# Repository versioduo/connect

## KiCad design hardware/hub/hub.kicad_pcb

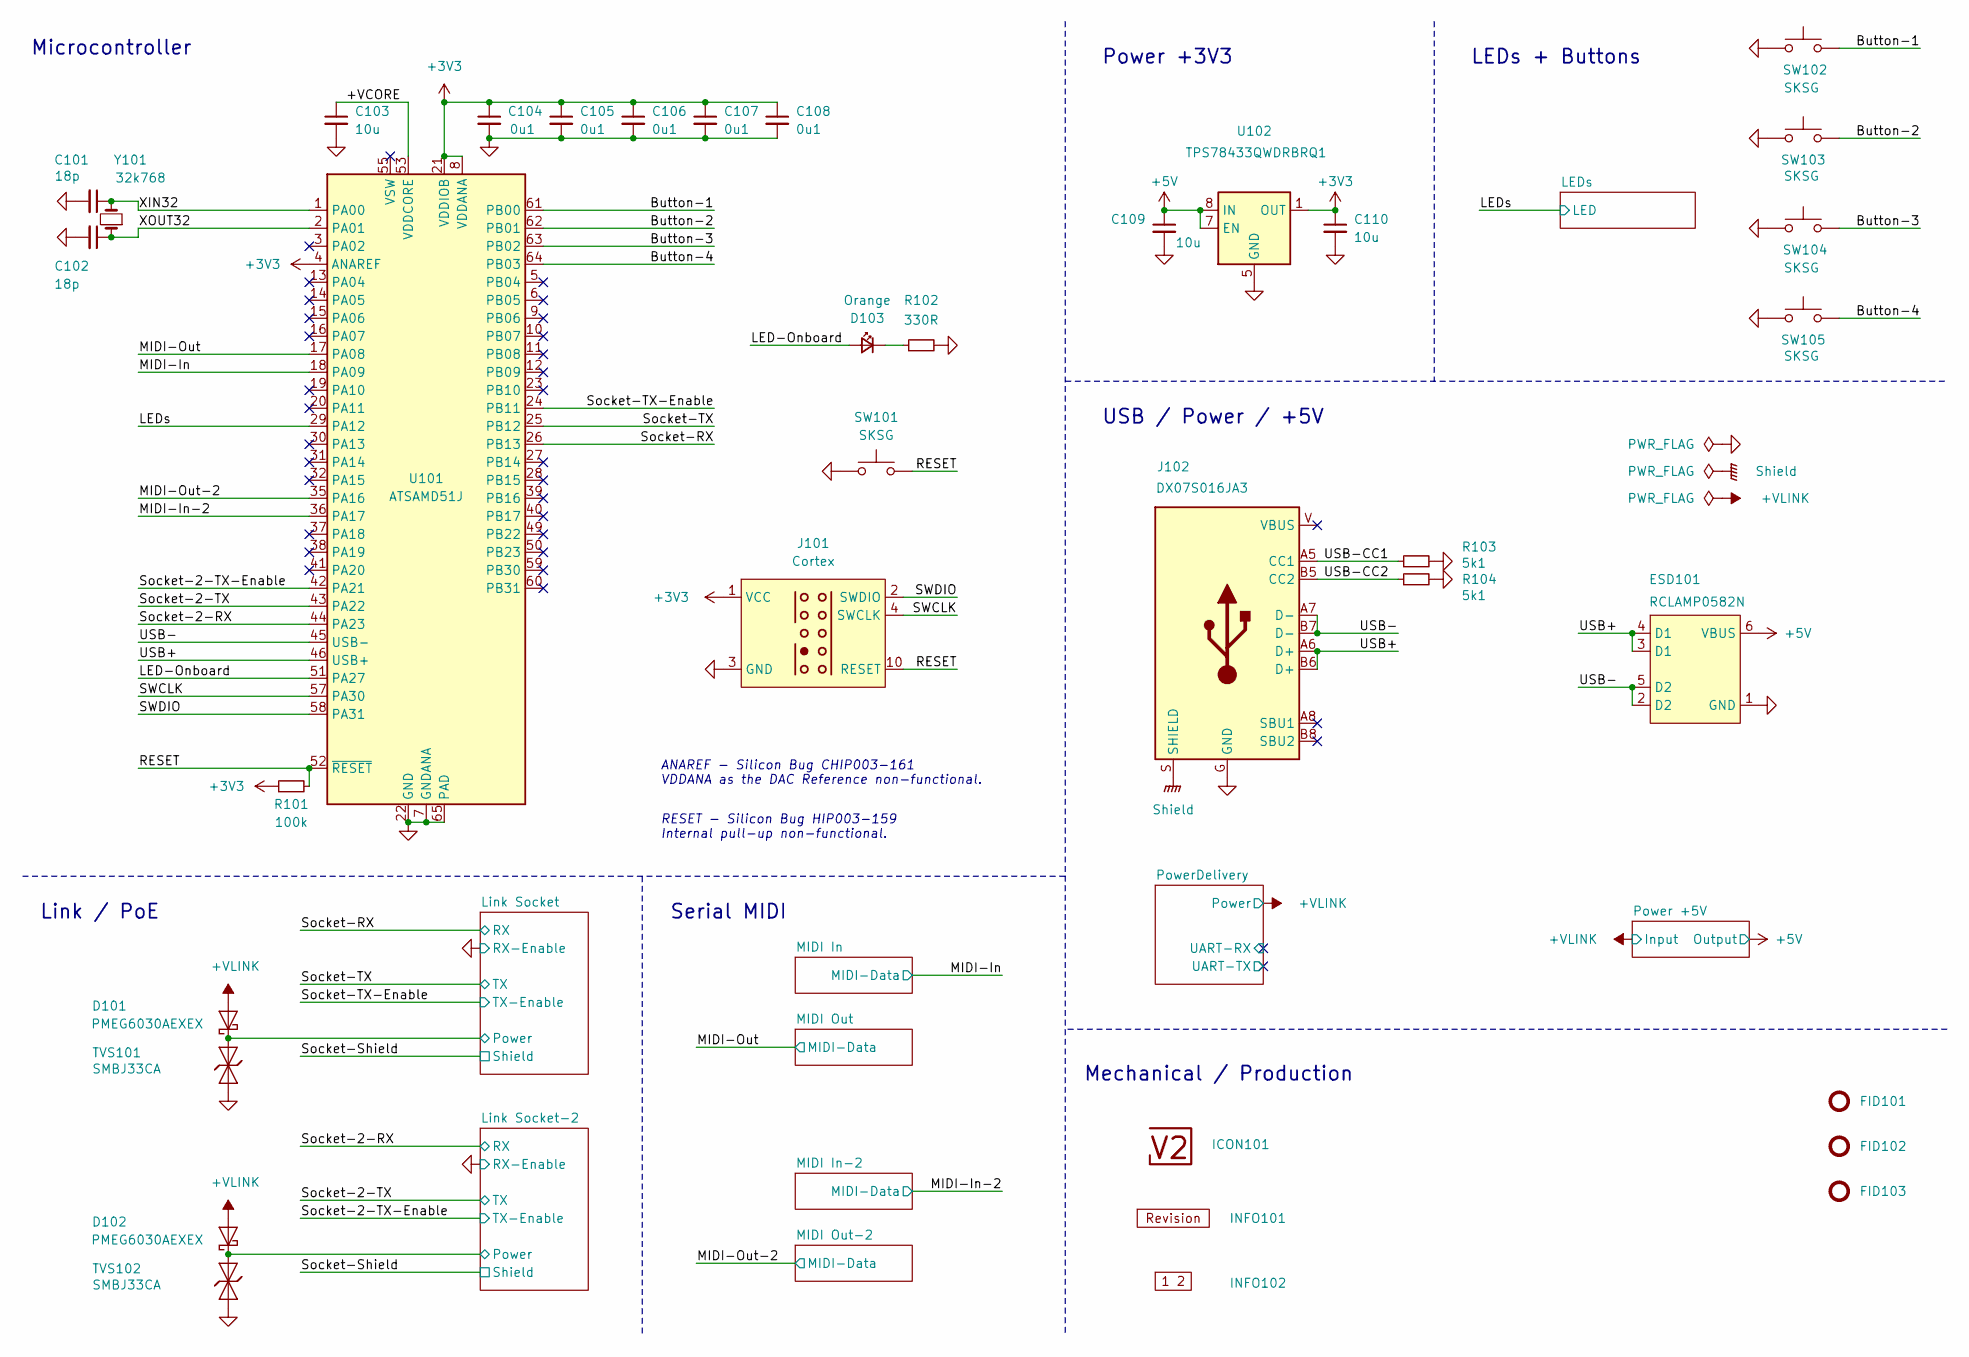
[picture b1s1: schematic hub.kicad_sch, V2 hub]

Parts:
C101, C102: 18p; C_1608; Rating 50V; Mouser 810-CGA3E2C0G1H180J
C103: 10u; C_1608; Rating 10V; Mouser 810-C1608X6S1A106M
C104, C105, C106, C107, C108: 0u1; C_1608; Rating 50V; Mouser 810-CGA3E2X7R1H104MA
C109, C110: 10u; C_2012; Rating 25V; Mouser 810-C2012X5R1E106K
D101, D102: PMEG6030AEXEX; D_SOD-123HP; Rating 60V; Mouser 771-PMEG6030AEXEX
D103: Orange; LED_1608; Rating 605nm; Mouser 755-SML-D12D1WT86
ESD101: RCLAMP0582N; SLP1210N6; Rating 20kV; Mouser 947-RCLAMP0582N.TCT
FID101, FID102, FID103: Fiducial_Paste; Fiducial_0.5mm_Mask1mm_Paste
ICON101: V2-logo; Logo_Small
INFO101: Revision
INFO102: Layer_Numbers-4
J101: Cortex
J102: DX07S016JA3; JAE_DX07S016JA3; Rating USB2.0; Mouser 656-DX07S016JA3R1500
R101: 100k; R_1608; Rating 100mW; Mouser 71-CRCW0603100KFKEAC
R102: 330R; R_1608; Rating 100mW; Mouser 71-CRCW0603330RFKEAC
R103, R104: 5k1; R_1608; Rating 100mW; Mouser 71-CRCW06035K10FKEAC
SW101, SW102, SW103, SW104, SW105: SKSG; Rating 1.6N; Mouser 688-SKSGACE010
TVS101, TVS102: SMBJ33CA; D_SMB; Rating 33V; Mouser 652-SMBJ33CA-Q
U101: ATSAMD51J; QFN-64-1EP_9x9mm_P0.5mm_EP4.8x4.8mm_ThermalVias; Rating Cortex-M4F; Mouser 556-ATSAMD51J19AMU
U102: TPS78433QWDRBRQ1; VSON-8-1_3x3mm_P0.65_EP1.65x2.4mm; Rating 300mA; Mouser 595-TPS78433QWDRBRQ1
Y101: 32k768; Crystal_SMD_3215-2Pin_3.2x1.5mm; Rating 10ppm; Mouser 815-ABS0716632.768KT

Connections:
+3V3: C104.1, C105.1, C106.1, C107.1, C108.1, C110.1, J101.1 (VCC), R101.1, U101.4 (ANAREF), U101.8 (VDDANA), U101.21 (VDDIOB), U101.34 (VDDIO), U101.48 (VDDIO), U101.56 (VDDIO), U102.1 (OUT); also elsewhere on the board
+5V: C109.1, ESD101.6 (VBUS), U102.7 (EN), U102.8 (IN); also elsewhere on the board
/+VCORE: C103.1, U101.53 (VDDCORE)
/+VLINK: D101.2 (A), D102.2 (A); also elsewhere on the board
/Button-1: SW102.2, U101.61 (PB00)
/Button-2: SW103.2, U101.62 (PB01)
/Button-3: SW104.2, U101.63 (PB02)
/Button-4: SW105.2, U101.64 (PB03)
/LED-Onboard: D103.2 (A), U101.51 (PA27)
/LEDs: U101.29 (PA12); also elsewhere on the board
/Link Socket-2/Power: D102.1 (K), TVS102.2 (A); also elsewhere on the board
/Link Socket/Power: D101.1 (K), TVS101.2 (A); also elsewhere on the board
/MIDI-In: U101.18 (PA09); also elsewhere on the board
/MIDI-In-2: U101.36 (PA17); also elsewhere on the board
/MIDI-Out: U101.17 (PA08); also elsewhere on the board
/MIDI-Out-2: U101.35 (PA16); also elsewhere on the board
/RESET: J101.10 (RESET), R101.2, SW101.2, U101.52 (~RESET)
/SWCLK: J101.4 (SWCLK), U101.57 (PA30)
/SWDIO: J101.2 (SWDIO), U101.58 (PA31)
/Shield: J102.S (SHIELD)
/Socket-2-RX: U101.44 (PA23); also elsewhere on the board
/Socket-2-TX: U101.43 (PA22); also elsewhere on the board
/Socket-2-TX-Enable: U101.42 (PA21); also elsewhere on the board
/Socket-RX: U101.26 (PB13); also elsewhere on the board
/Socket-TX: U101.25 (PB12); also elsewhere on the board
/Socket-TX-Enable: U101.24 (PB11); also elsewhere on the board
/USB+: ESD101.3 (D1), ESD101.4 (D1), J102.A6 (D+), J102.B6 (D+), U101.46 (USB+)
/USB-: ESD101.2 (D2), ESD101.5 (D2), J102.A7 (D-), J102.B7 (D-), U101.45 (USB-)
/USB-CC1: J102.A5 (CC1), R103.1
/USB-CC2: J102.B5 (CC2), R104.1
/XIN32: C101.1, U101.1 (PA00), Y101.2
/XOUT32: C102.1, U101.2 (PA01), Y101.1
GND: C101.2, C102.2, C103.2, C104.2, C105.2, C106.2, C107.2, C108.2, C109.2, C110.2, ESD101.1 (GND), J101.3 (GND), J101.5 (GND), J102.G (GND), R102.2, R103.2, R104.2, SW101.1, SW102.1, SW103.1, SW104.1, SW105.1, TVS101.1 (K), TVS102.1 (K), U101.7 (GNDANA), U101.22 (GND), U101.33 (GND), U101.47 (GND), U101.54 (GND), U101.65 (PAD), U102.5 (GND), U102.9 (GND); also elsewhere on the board
unnamed: D103.1 (K), R102.1

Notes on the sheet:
ANAREF - Silicon Bug CHIP003-161 VDDANA as the DAC Reference non-functional.
Link / PoE
RESET - Silicon Bug HIP003-159 Internal pull-up non-functional.
LEDs + Buttons
Serial MIDI
Power +3V3
Mechanical / Production
Microcontroller
USB / Power / +5V

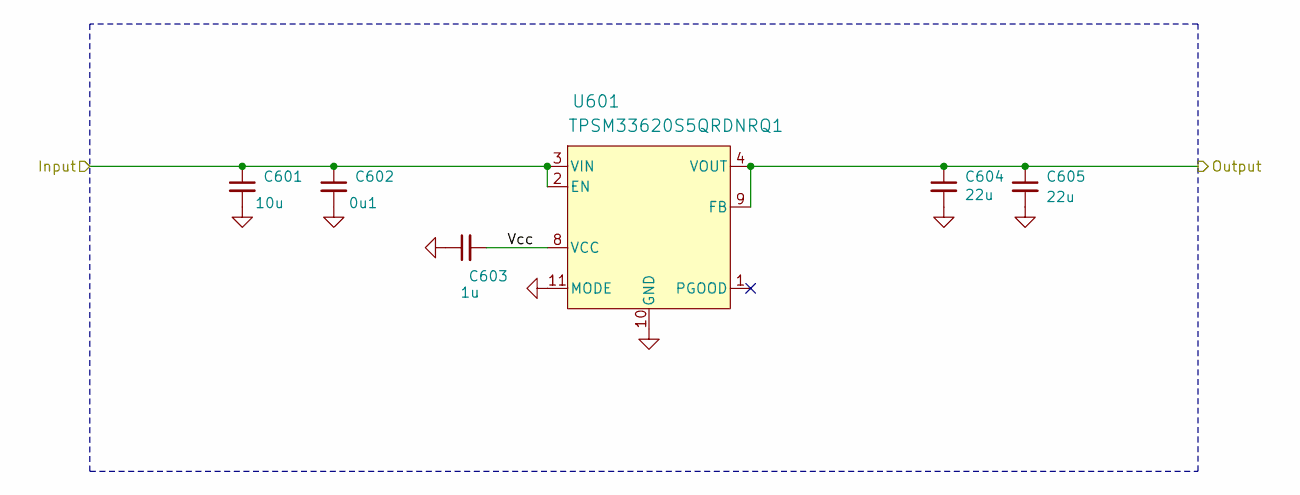
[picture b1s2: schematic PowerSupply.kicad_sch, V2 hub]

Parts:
C601: 10u; C_3225; Rating 50V; Mouser 810-CNC6P1X7R1H106K2
C602: 0u1; C_1608; Rating 50V; Mouser 810-CGA3E2X7R1H104MA
C603: 1u; C_1608; Rating 50V; Mouser 810-CGA3E3X7R1H105K0
C604, C605: 22u; C_3225; Rating 25V; Mouser 810-CGA6P3X7R1E226M5
U601: TPSM33620S5QRDNRQ1; QFN-11; Rating 2A; Mouser 595-SM33620S5QRDNRQ1

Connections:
+5V: C604.1, C605.1, U601.4 (VOUT), U601.9 (FB); also elsewhere on the board
/+VLINK: C601.1, C602.1, U601.2 (EN), U601.3 (VIN); also elsewhere on the board
/Power +5V/Vcc: C603.2, U601.8 (VCC)
GND: C601.2, C602.2, C603.1, C604.2, C605.2, U601.10 (GND), U601.11 (MODE); also elsewhere on the board

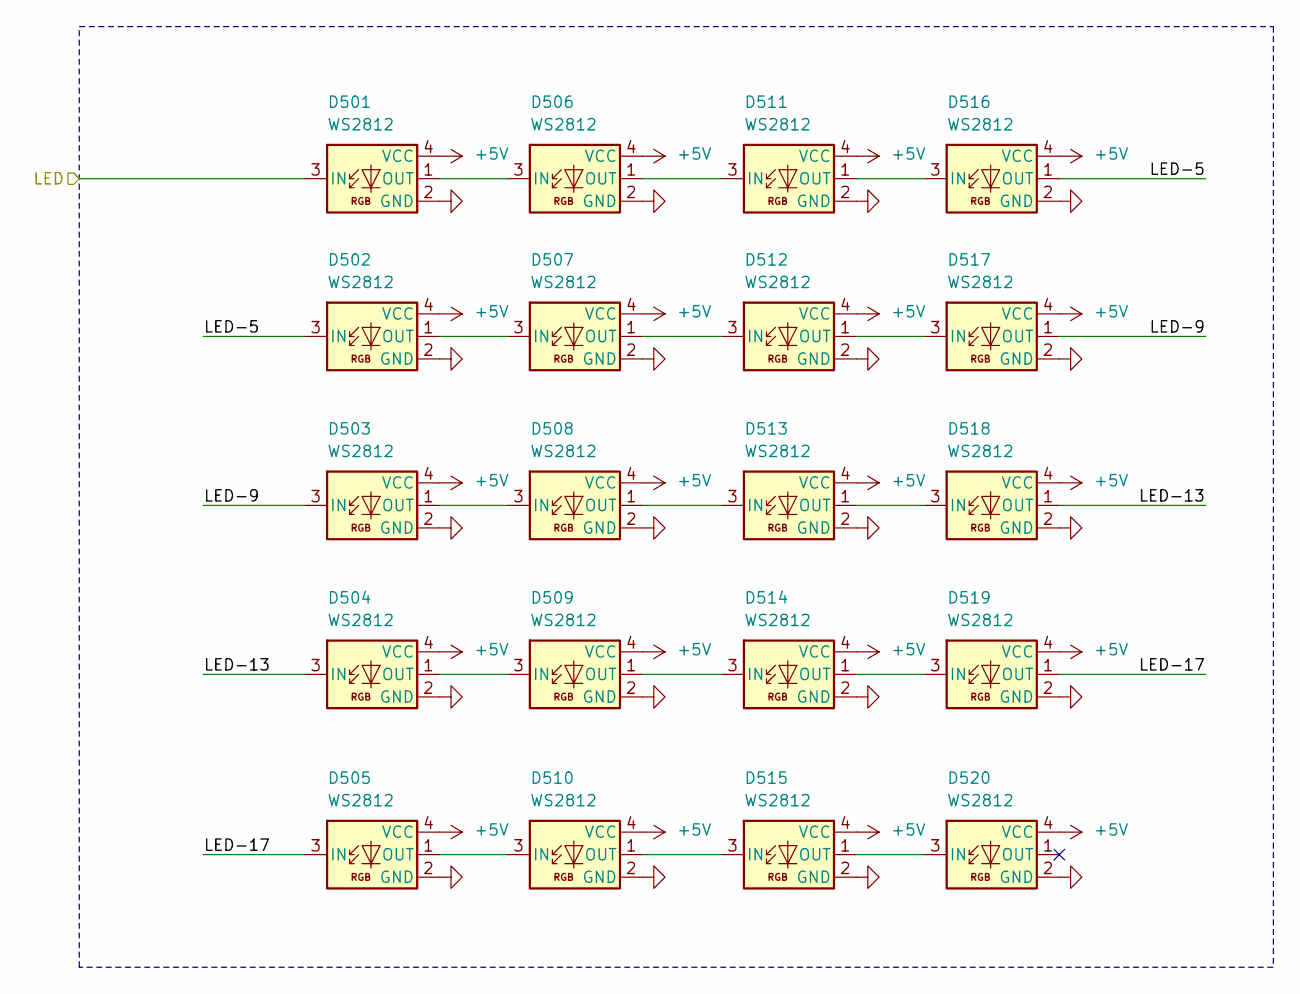
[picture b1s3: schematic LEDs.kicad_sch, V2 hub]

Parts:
D501, D502, D503, D504, D505, D506, D507, D508, D509, D510, D511, D512, D513, D514, D515, D516, D517, D518, D519, D520: WS2812; WS2812-2020; Rating 15mA; LCSC C965555

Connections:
+5V: D501.4 (VCC), D502.4 (VCC), D503.4 (VCC), D504.4 (VCC), D505.4 (VCC), D506.4 (VCC), D507.4 (VCC), D508.4 (VCC), D509.4 (VCC), D510.4 (VCC), D511.4 (VCC), D512.4 (VCC), D513.4 (VCC), D514.4 (VCC), D515.4 (VCC), D516.4 (VCC), D517.4 (VCC), D518.4 (VCC), D519.4 (VCC), D520.4 (VCC); also elsewhere on the board
/LEDs: D501.3 (IN); also elsewhere on the board
/LEDs/LED-5: D502.3 (IN), D516.1 (OUT)
/LEDs/LED-9: D503.3 (IN), D517.1 (OUT)
/LEDs/LED-13: D504.3 (IN), D518.1 (OUT)
/LEDs/LED-17: D505.3 (IN), D519.1 (OUT)
GND: D501.2 (GND), D502.2 (GND), D503.2 (GND), D504.2 (GND), D505.2 (GND), D506.2 (GND), D507.2 (GND), D508.2 (GND), D509.2 (GND), D510.2 (GND), D511.2 (GND), D512.2 (GND), D513.2 (GND), D514.2 (GND), D515.2 (GND), D516.2 (GND), D517.2 (GND), D518.2 (GND), D519.2 (GND), D520.2 (GND); also elsewhere on the board
unnamed: D501.1 (OUT), D506.3 (IN)
unnamed: D502.1 (OUT), D507.3 (IN)
unnamed: D503.1 (OUT), D508.3 (IN)
unnamed: D504.1 (OUT), D509.3 (IN)
unnamed: D505.1 (OUT), D510.3 (IN)
unnamed: D506.1 (OUT), D511.3 (IN)
unnamed: D507.1 (OUT), D512.3 (IN)
unnamed: D508.1 (OUT), D513.3 (IN)
unnamed: D509.1 (OUT), D514.3 (IN)
unnamed: D510.1 (OUT), D515.3 (IN)
unnamed: D511.1 (OUT), D516.3 (IN)
unnamed: D512.1 (OUT), D517.3 (IN)
unnamed: D513.1 (OUT), D518.3 (IN)
unnamed: D514.1 (OUT), D519.3 (IN)
unnamed: D515.1 (OUT), D520.3 (IN)

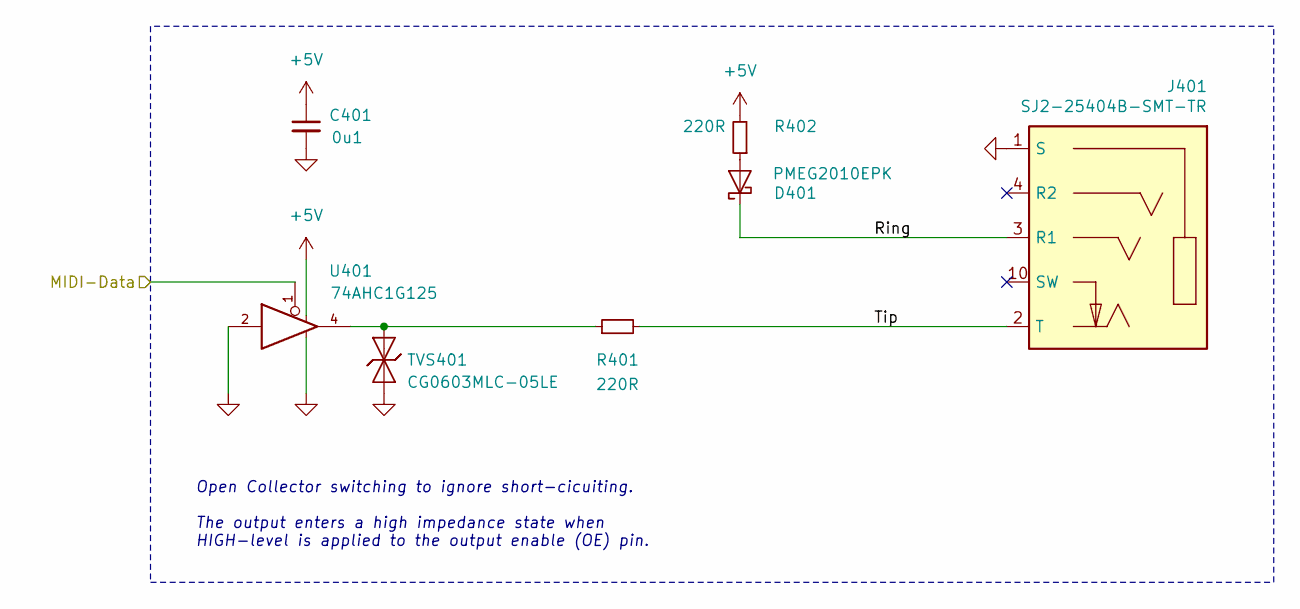
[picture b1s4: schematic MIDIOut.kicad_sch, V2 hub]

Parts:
C401: 0u1; C_1608; Rating 50V; Mouser 810-CGA3E2X7R1H104MA
D401: PMEG2010EPK; D_SOD-1608; Rating 20V; Mouser 771-PMEG2010EPK
J401: SJ2-25404B-SMT-TR; CUI_SJ2-25404B-SMT-TR; Rating 2.5mm; Mouser 490-SJ2-25404BSMT-TR
R401, R402: 220R; R_1608; Rating 330mW; Mouser 71-CRCW0603220RFKEAH
TVS401: CG0603MLC-05LE; D_1608; Rating 5V; Mouser 652-CG0603MLC-05LE
U401: 74AHC1G125; SOT-23-5; Rating 8mA; Mouser 595-SN74AHC1G125DBVR

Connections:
+5V: C401.1, R402.2, U401.5; also elsewhere on the board
/MIDI Out/Ring: D401.1 (K), J401.3 (R1)
/MIDI Out/Tip: J401.2 (T), R401.2
/MIDI-Out: U401.1; also elsewhere on the board
GND: C401.2, J401.1 (S), TVS401.1 (K), U401.2, U401.3; also elsewhere on the board
unnamed: D401.2 (A), R402.1
unnamed: R401.1, TVS401.2 (A), U401.4

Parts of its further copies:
C901: 0u1; C_1608; Rating 50V; Mouser 810-CGA3E2X7R1H104MA
D901: PMEG2010EPK; D_SOD-1608; Rating 20V; Mouser 771-PMEG2010EPK
J901: SJ2-25404B-SMT-TR; CUI_SJ2-25404B-SMT-TR; Rating 2.5mm; Mouser 490-SJ2-25404BSMT-TR
R901, R902: 220R; R_1608; Rating 330mW; Mouser 71-CRCW0603220RFKEAH
TVS901: CG0603MLC-05LE; D_1608; Rating 5V; Mouser 652-CG0603MLC-05LE
U901: 74AHC1G125; SOT-23-5; Rating 8mA; Mouser 595-SN74AHC1G125DBVR

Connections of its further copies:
+5V: C901.1, R902.2, U901.5; also elsewhere on the board
/MIDI Out-2/Ring: D901.1 (K), J901.3 (R1)
/MIDI Out-2/Tip: J901.2 (T), R901.2
/MIDI-Out-2: U901.1; also elsewhere on the board
GND: C901.2, J901.1 (S), TVS901.1 (K), U901.2, U901.3; also elsewhere on the board
unnamed: D901.2 (A), R902.1
unnamed: R901.1, TVS901.2 (A), U901.4

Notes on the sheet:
﻿Open Collector switching to ignore short-cicuiting. The output enters a high impedance state when HIGH-level is applied to the output enable (OE) pin.

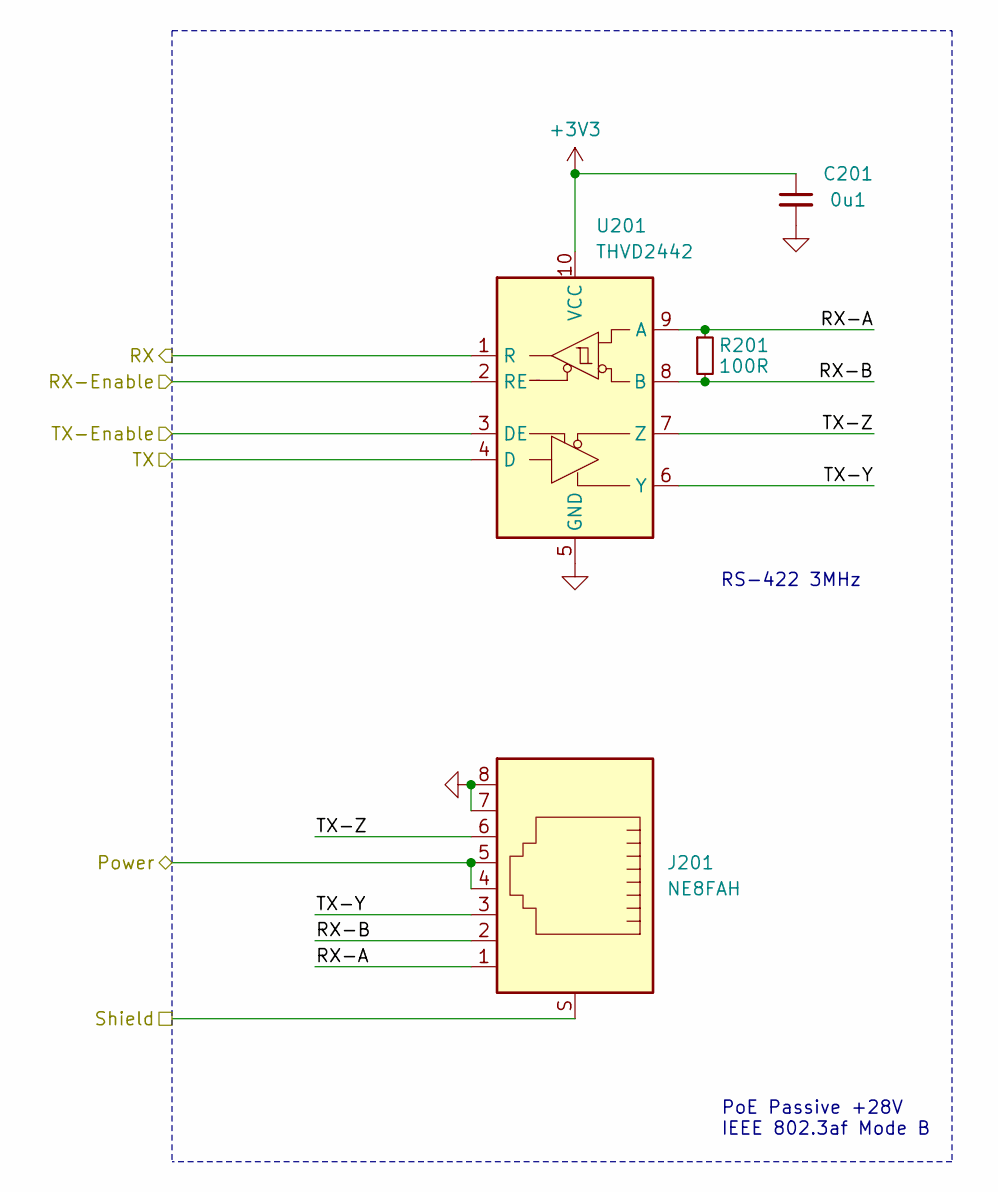
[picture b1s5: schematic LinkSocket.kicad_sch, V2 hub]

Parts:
C201: 0u1; C_1608; Rating 50V; Mouser 810-CGA3E2X7R1H104MA
J201: NE8FAH; Rating CAT5e; Mouser 568-NE8FAH
R201: 100R; R_1608; Rating 330mW; Mouser 71-CRCW0603100RFKEAH
U201: THVD2442; VSON-10-4-1EP_3x3mm_P0.5mm_EP1.65x2.4mm_ThermalVias; Rating 20Mbps; Mouser 595-THVD2442DRCR

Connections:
+3V3: C201.1, U201.10 (VCC); also elsewhere on the board
/Link Socket/Power: J201.4, J201.5; also elsewhere on the board
/Link Socket/RX-A: J201.1, R201.1, U201.9 (A)
/Link Socket/RX-B: J201.2, R201.2, U201.8 (B)
/Link Socket/TX-Y: J201.3, U201.6 (Y)
/Link Socket/TX-Z: J201.6, U201.7 (Z)
/Socket-RX: U201.1 (R); also elsewhere on the board
/Socket-Shield: J201.S; also elsewhere on the board
/Socket-TX: U201.4 (D); also elsewhere on the board
/Socket-TX-Enable: U201.3 (DE); also elsewhere on the board
GND: C201.2, J201.7, J201.8, U201.2 (RE), U201.5 (GND), U201.11 (GND); also elsewhere on the board

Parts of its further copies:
C701: 0u1; C_1608; Rating 50V; Mouser 810-CGA3E2X7R1H104MA
J701: NE8FAH; Rating CAT5e; Mouser 568-NE8FAH
R701: 100R; R_1608; Rating 330mW; Mouser 71-CRCW0603100RFKEAH
U701: THVD2442; VSON-10-4-1EP_3x3mm_P0.5mm_EP1.65x2.4mm_ThermalVias; Rating 20Mbps; Mouser 595-THVD2442DRCR

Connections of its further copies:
+3V3: C701.1, U701.10 (VCC); also elsewhere on the board
/Link Socket-2/Power: J701.4, J701.5; also elsewhere on the board
/Link Socket-2/RX-A: J701.1, R701.1, U701.9 (A)
/Link Socket-2/RX-B: J701.2, R701.2, U701.8 (B)
/Link Socket-2/TX-Y: J701.3, U701.6 (Y)
/Link Socket-2/TX-Z: J701.6, U701.7 (Z)
/Socket-2-RX: U701.1 (R); also elsewhere on the board
/Socket-2-TX: U701.4 (D); also elsewhere on the board
/Socket-2-TX-Enable: U701.3 (DE); also elsewhere on the board
/Socket-Shield: J701.S; also elsewhere on the board
GND: C701.2, J701.7, J701.8, U701.2 (RE), U701.5 (GND), U701.11 (GND); also elsewhere on the board

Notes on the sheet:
PoE Passive +28V IEEE 802.3af Mode B
RS-422 3MHz

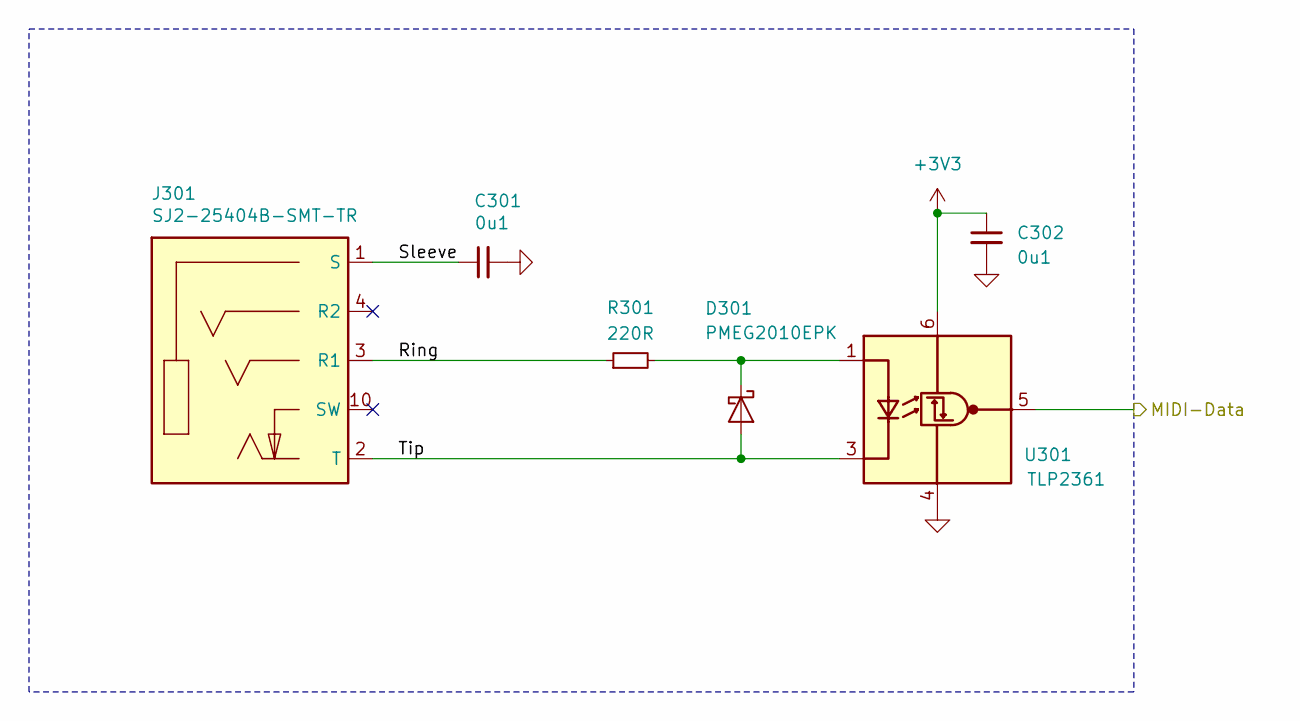
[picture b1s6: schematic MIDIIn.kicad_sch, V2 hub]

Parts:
C301, C302: 0u1; C_1608; Rating 50V; Mouser 810-CGA3E2X7R1H104MA
D301: PMEG2010EPK; D_SOD-1608; Rating 20V; Mouser 771-PMEG2010EPK
J301: SJ2-25404B-SMT-TR; CUI_SJ2-25404B-SMT-TR; Rating 2.5mm; Mouser 490-SJ2-25404BSMT-TR
R301: 220R; R_1608; Rating 330mW; Mouser 71-CRCW0603220RFKEAH
U301: TLP2361; SO-5-6_4.55x3.7mm_P1.27mm; Rating 15Mbps; Mouser 757-TLP2361TPRE

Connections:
+3V3: C302.1, U301.6 (VDD); also elsewhere on the board
/MIDI In/Ring: J301.3 (R1), R301.1
/MIDI In/Sleeve: C301.1, J301.1 (S)
/MIDI In/Tip: D301.2 (A), J301.2 (T), U301.3 (K)
/MIDI-In: U301.5 (VO); also elsewhere on the board
GND: C301.2, C302.2, U301.4 (GND); also elsewhere on the board
unnamed: D301.1 (K), R301.2, U301.1 (A)

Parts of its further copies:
C801, C802: 0u1; C_1608; Rating 50V; Mouser 810-CGA3E2X7R1H104MA
D801: PMEG2010EPK; D_SOD-1608; Rating 20V; Mouser 771-PMEG2010EPK
J801: SJ2-25404B-SMT-TR; CUI_SJ2-25404B-SMT-TR; Rating 2.5mm; Mouser 490-SJ2-25404BSMT-TR
R801: 220R; R_1608; Rating 330mW; Mouser 71-CRCW0603220RFKEAH
U801: TLP2361; SO-5-6_4.55x3.7mm_P1.27mm; Rating 15Mbps; Mouser 757-TLP2361TPRE

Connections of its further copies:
+3V3: C802.1, U801.6 (VDD); also elsewhere on the board
/MIDI In-2/Ring: J801.3 (R1), R801.1
/MIDI In-2/Sleeve: C801.1, J801.1 (S)
/MIDI In-2/Tip: D801.2 (A), J801.2 (T), U801.3 (K)
/MIDI-In-2: U801.5 (VO); also elsewhere on the board
GND: C801.2, C802.2, U801.4 (GND); also elsewhere on the board
unnamed: D801.1 (K), R801.2, U801.1 (A)

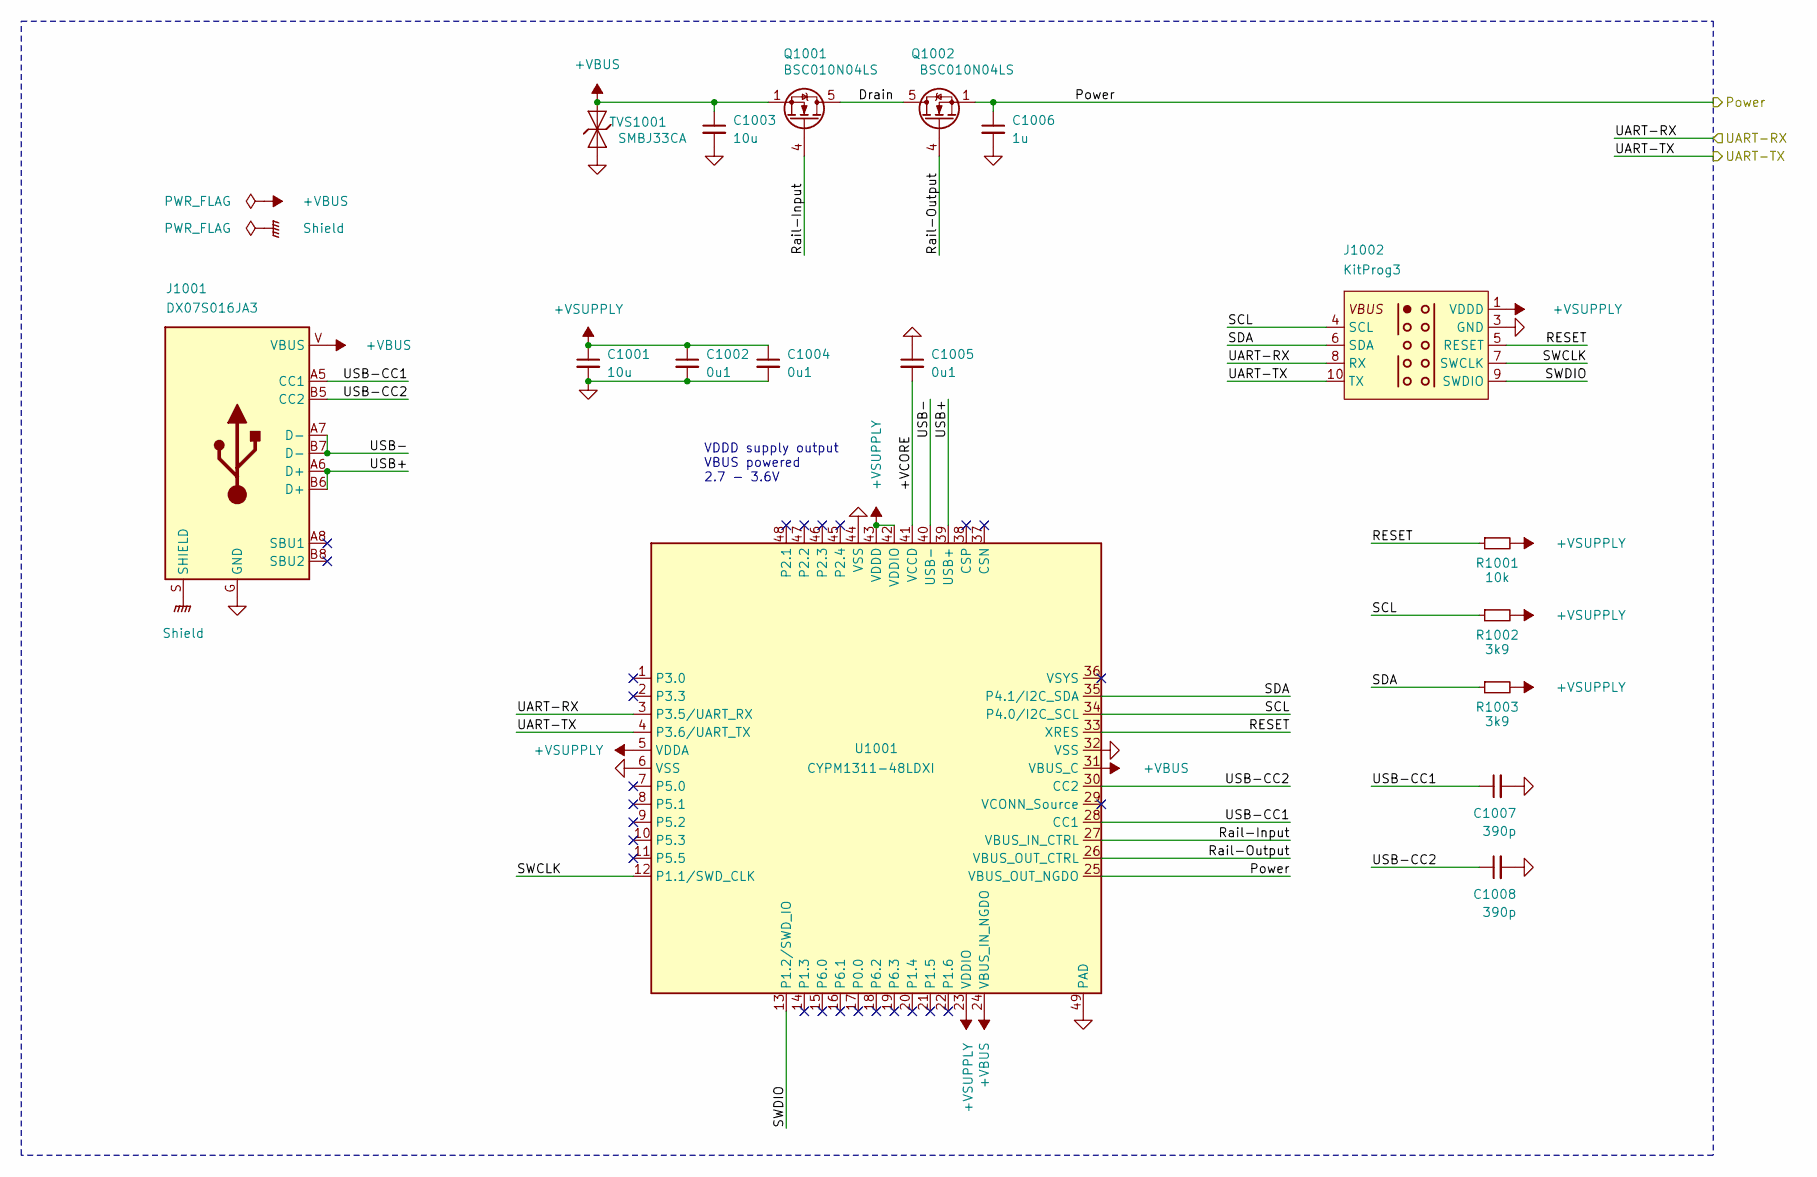
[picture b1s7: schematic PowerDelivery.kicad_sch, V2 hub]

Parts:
C1001: 10u; C_1608; Rating 10V; Mouser 810-C1608X6S1A106M
C1002, C1004, C1005: 0u1; C_1608; Rating 50V; Mouser 810-CGA3E2X7R1H104MA
C1003: 10u; C_2012; Rating 25V; Mouser 810-C2012X5R1E106K
C1006: 1u; C_1608; Rating 50V; Mouser 810-CGA3E3X7R1H105K0
C1007, C1008: 390p; C_1608; Rating 50V; Mouser 810-CGA3E2C0G1H391J
J1001: DX07S016JA3; JAE_DX07S016JA3; Rating USB2.0; Mouser 656-DX07S016JA3R1500
J1002: KitProg3
Q1001, Q1002: BSC010N04LS; TDSON-8-FL; Rating 40V; Mouser 726-BSC010N04LS
R1001: 10k; R_1608; Rating 100mW; Mouser 71-CRCW060310K0FKEAC
R1002, R1003: 3k9; R_1608; Rating 100mW; Mouser 71-CRCW06033K90FKEAC
TVS1001: SMBJ33CA; D_SMB; Rating 33V; Mouser 652-SMBJ33CA-Q
U1001: CYPM1311-48LDXI; QFN-48-1EP_6x6mm_P0.4mm_EP4.6x4.6mm; Rating 28V; Mouser 727-CYPM1311-48LDXI

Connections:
/+VLINK: C1006.1, Q1002.1 (S), U1001.25 (VBUS_OUT_NGDO); also elsewhere on the board
/PowerDelivery/+VBUS: C1003.1, J1001.V (VBUS), Q1001.1 (S), TVS1001.2 (A), U1001.24 (VBUS_IN_NGDO), U1001.31 (VBUS_C)
/PowerDelivery/+VCORE: C1005.2, U1001.41 (VCCD)
/PowerDelivery/+VSUPPLY: C1001.1, C1002.1, C1004.1, J1002.1 (VDDD), R1001.2, R1002.2, R1003.2, U1001.5 (VDDA), U1001.23 (VDDIO), U1001.42 (VDDIO), U1001.43 (VDDD)
/PowerDelivery/Drain: Q1001.5 (D), Q1002.5 (D)
/PowerDelivery/RESET: J1002.5 (RESET), R1001.1, U1001.33 (XRES)
/PowerDelivery/Rail-Input: Q1001.4 (G), U1001.27 (VBUS_IN_CTRL)
/PowerDelivery/Rail-Output: Q1002.4 (G), U1001.26 (VBUS_OUT_CTRL)
/PowerDelivery/SCL: J1002.4 (SCL), R1002.1, U1001.34 (P4.0/I2C_SCL)
/PowerDelivery/SDA: J1002.6 (SDA), R1003.1, U1001.35 (P4.1/I2C_SDA)
/PowerDelivery/SWCLK: J1002.7 (SWCLK), U1001.12 (P1.1/SWD_CLK)
/PowerDelivery/SWDIO: J1002.9 (SWDIO), U1001.13 (P1.2/SWD_IO)
/PowerDelivery/Shield: J1001.S (SHIELD)
/PowerDelivery/UART-RX: J1002.8 (RX), U1001.3 (P3.5/UART_RX)
/PowerDelivery/UART-TX: J1002.10 (TX), U1001.4 (P3.6/UART_TX)
/PowerDelivery/USB+: J1001.A6 (D+), J1001.B6 (D+), U1001.39 (USB+)
/PowerDelivery/USB-: J1001.A7 (D-), J1001.B7 (D-), U1001.40 (USB-)
/PowerDelivery/USB-CC1: C1007.1, J1001.A5 (CC1), U1001.28 (CC1)
/PowerDelivery/USB-CC2: C1008.1, J1001.B5 (CC2), U1001.30 (CC2)
GND: C1001.2, C1002.2, C1003.2, C1004.2, C1005.1, C1006.2, C1007.2, C1008.2, J1001.G (GND), J1002.3 (GND), TVS1001.1 (K), U1001.6 (VSS), U1001.32 (VSS), U1001.44 (VSS), U1001.49 (PAD); also elsewhere on the board

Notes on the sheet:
VDDD supply output VBUS powered 2.7 - 3.6V

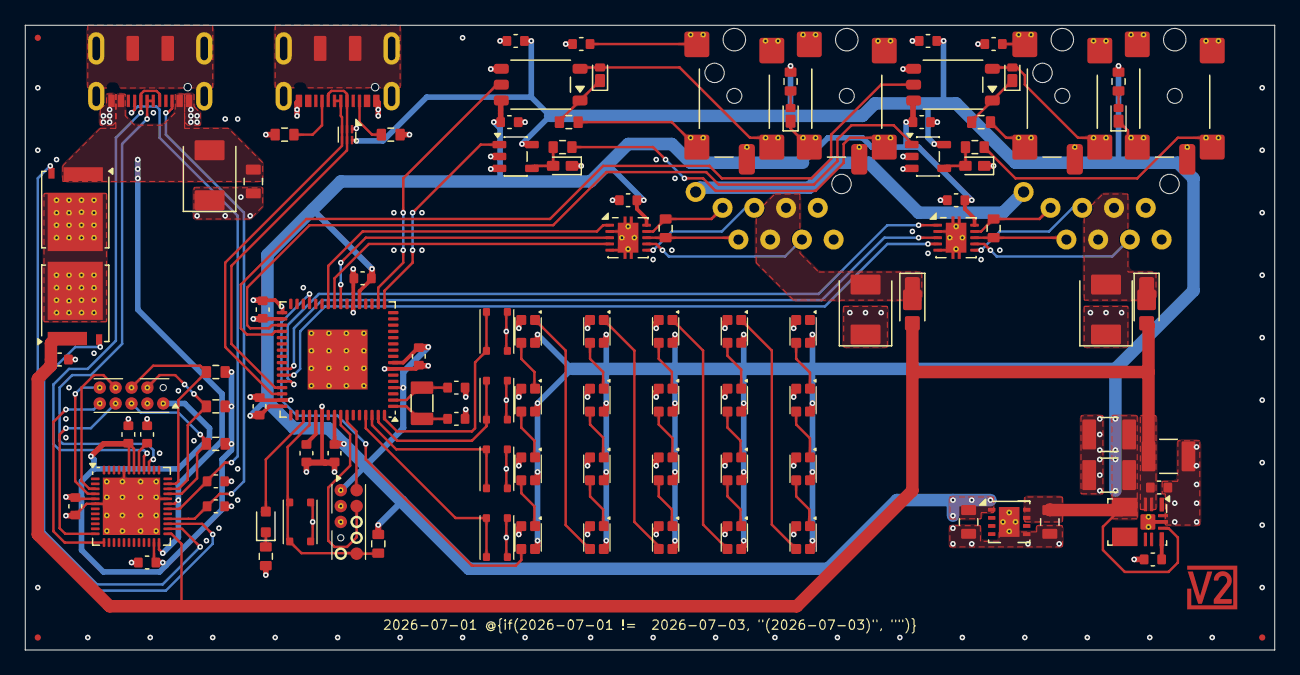
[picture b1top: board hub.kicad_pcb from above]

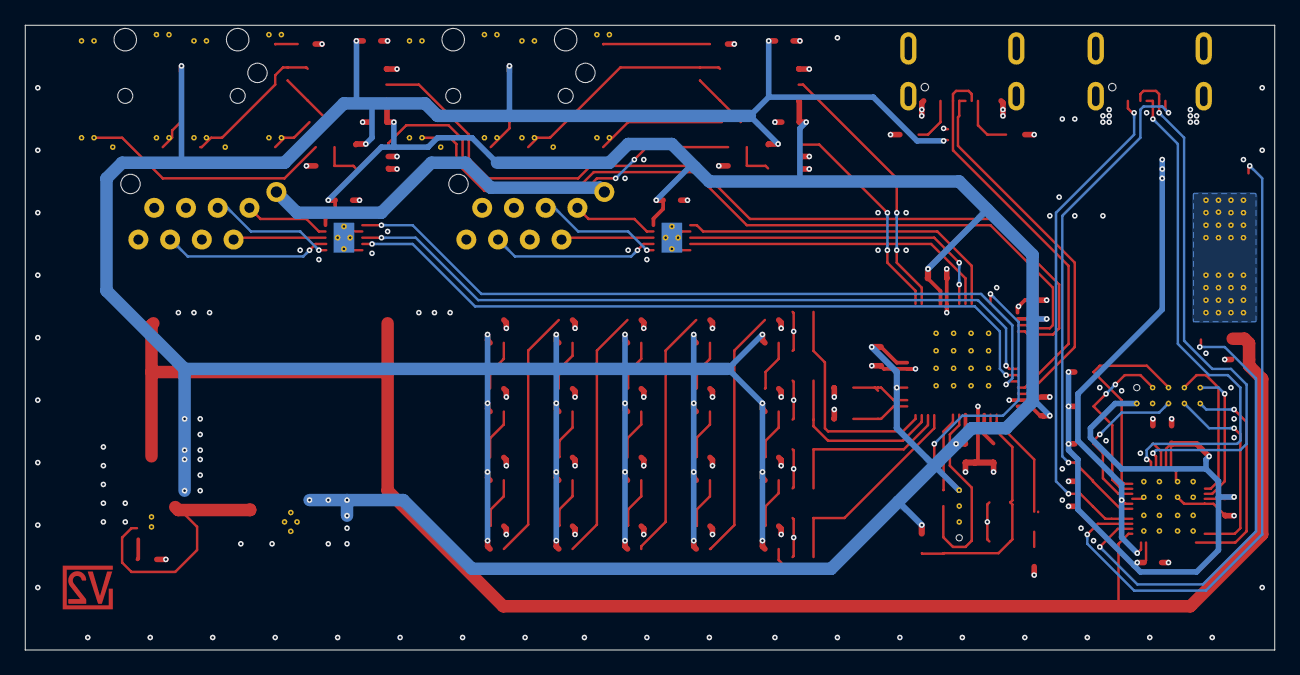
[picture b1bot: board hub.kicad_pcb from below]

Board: 4 copper layers, 100.0 x 50.0 mm, 113 parts (2 on the bottom side), 95 nets.
